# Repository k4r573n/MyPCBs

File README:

*******************************************
***   M y   P C B   L a y o u t s       ***
*******************************************

this will become an PCB Layout collection of Projects
I have done.

Since EAGLE provide XML-Files it is easy to use them
with version control systems what I'm doing here.

for suggestions or fixes contact me
Karsten Hinz <k.hinz@tu-bs.de>

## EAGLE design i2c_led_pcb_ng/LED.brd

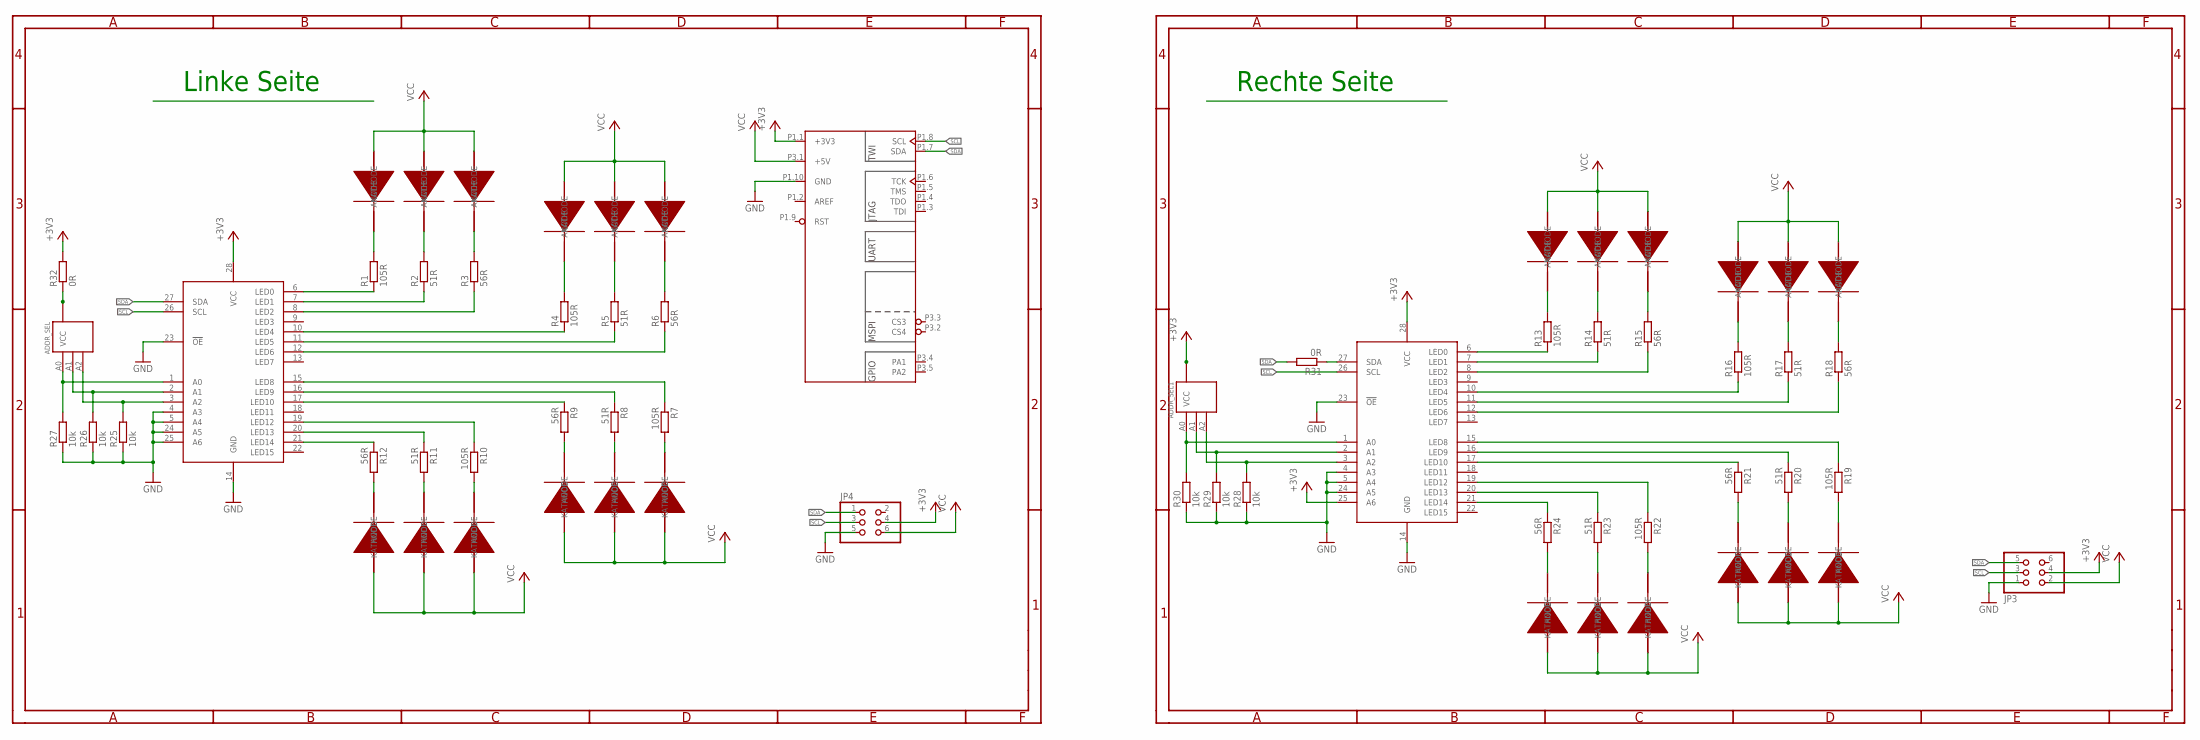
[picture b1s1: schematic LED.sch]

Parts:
ADDR_SEL, ADDR_SEL1: ADDR_SEL
JP3, JP4: PINHD-2X3_2.54-90°; 2X03/90
R1, R4, R7, R10, R13, R16, R19, R22: 105R; R0603
R2, R5, R8, R11, R14, R17, R20, R23: 51R; R0603
R3, R6, R9, R12, R15, R18, R21, R24: 56R; R0603
R25, R27: 10k; R0402
R26, R28, R29, R30: 10k; R0603
R31, R32: 0R; R0603
U$1, U$2, U$3, U$4, U$11, U$12, U$13, U$14: RGB-LED; PLCC_SMD_LED_RGB
U$6: INGA_OHNE_JP2; INGA_JP1_JP3
U$9, U$15: PCA9635; TSSOP28

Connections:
+3V3: JP3.4, JP4.4, R32.2, U$6.P1.1 (+3V3), U$9.28 (VCC), U$15.28 (VCC)
BLA: ADDR_SEL.VCC, ADDR_SEL.VCC@1 (VCC), ADDR_SEL.VCC@2 (VCC), R32.1
GND: JP3.1, JP4.5, R25.1, R26.1, R27.1, R28.1, R29.1, R30.1, U$6.P1.10 (GND), U$9.4 (A3), U$9.5 (A4), U$9.14 (GND), U$9.23 (!OE), U$9.24 (A5), U$9.25 (A6), U$15.4 (A3), U$15.5 (A4), U$15.14 (GND), U$15.23 (!OE), U$15.24 (A5)
unnamed: R1.1, U$9.6 (LED0)
unnamed: R2.1, U$9.7 (LED1)
unnamed: R3.1, U$9.8 (LED2)
unnamed: R4.1, U$9.10 (LED4)
unnamed: R5.1, U$9.11 (LED5)
unnamed: R6.1, U$9.12 (LED6)
unnamed: R7.1, U$9.15 (LED8)
unnamed: R8.1, U$9.16 (LED9)
unnamed: R9.1, U$9.17 (LED10)
unnamed: R10.1, U$9.19 (LED12)
unnamed: R11.1, U$9.20 (LED13)
unnamed: R12.1, U$9.21 (LED14)
unnamed: R12.2, U$4.P1 (KATHODE)
unnamed: R11.2, U$4.P2 (KATHODE)
unnamed: R10.2, U$4.P3 (KATHODE)
unnamed: R7.2, U$3.P3 (KATHODE)
unnamed: R8.2, U$3.P2 (KATHODE)
unnamed: R2.2, U$1.P2 (KATHODE)
unnamed: R1.2, U$1.P3 (KATHODE)
unnamed: R3.2, U$1.P1 (KATHODE)
unnamed: R4.2, U$2.P3 (KATHODE)
unnamed: R5.2, U$2.P2 (KATHODE)
unnamed: R6.2, U$2.P1 (KATHODE)
unnamed: R13.2, U$11.P3 (KATHODE)
unnamed: R13.1, U$15.6 (LED0)
unnamed: R14.1, U$15.7 (LED1)
unnamed: R15.1, U$15.8 (LED2)
unnamed: R16.1, U$15.10 (LED4)
unnamed: R17.1, U$15.11 (LED5)
unnamed: R18.1, U$15.12 (LED6)
unnamed: R19.1, U$15.15 (LED8)
unnamed: R20.1, U$15.16 (LED9)
unnamed: R21.1, U$15.17 (LED10)
unnamed: R22.1, U$15.19 (LED12)
unnamed: R23.1, U$15.20 (LED13)
unnamed: R24.1, U$15.21 (LED14)
unnamed: R14.2, U$11.P2 (KATHODE)
unnamed: R15.2, U$11.P1 (KATHODE)
unnamed: R16.2, U$12.P3 (KATHODE)
unnamed: R17.2, U$12.P2 (KATHODE)
unnamed: R18.2, U$12.P1 (KATHODE)
unnamed: R24.2, U$14.P1 (KATHODE)
unnamed: R23.2, U$14.P2 (KATHODE)
unnamed: R22.2, U$14.P3 (KATHODE)
unnamed: R21.2, U$13.P1 (KATHODE)
unnamed: R20.2, U$13.P2 (KATHODE)
unnamed: R19.2, U$13.P3 (KATHODE)
unnamed: R9.2, U$3.P1 (KATHODE)
unnamed: ADDR_SEL.A2, R25.2, U$9.3 (A2)
unnamed: ADDR_SEL.A1, R26.2, U$9.2 (A1)
unnamed: ADDR_SEL.A0, R27.2, U$9.1 (A0)
unnamed: ADDR_SEL1.A2, R28.2, U$15.3 (A2)
unnamed: ADDR_SEL1.A1, R29.2, U$15.2 (A1)
unnamed: ADDR_SEL1.A0, R30.2, U$15.1 (A0)
SCL: JP3.3, JP4.3, U$6.P1.8 (SCL), U$9.26 (SCL), U$15.26 (SCL)
SDA: JP3.5, JP4.1, R31.2, U$6.P1.7 (SDA), U$9.27 (SDA)
SDA@1: R31.1, U$15.27 (SDA)
VCC: ADDR_SEL1.VCC, ADDR_SEL1.VCC@1 (VCC), ADDR_SEL1.VCC@2 (VCC), JP3.2, JP4.6, U$1.P4 (ANODE), U$1.P5 (ANODE), U$1.P6 (ANODE), U$2.P4 (ANODE), U$2.P5 (ANODE), U$2.P6 (ANODE), U$3.P4 (ANODE), U$3.P5 (ANODE), U$3.P6 (ANODE), U$4.P4 (ANODE), U$4.P5 (ANODE), U$4.P6 (ANODE), U$6.P3.1 (+5V), U$11.P4 (ANODE), U$11.P5 (ANODE), U$11.P6 (ANODE), U$12.P4 (ANODE), U$12.P5 (ANODE), U$12.P6 (ANODE), U$13.P4 (ANODE), U$13.P5 (ANODE), U$13.P6 (ANODE), U$14.P4 (ANODE), U$14.P5 (ANODE), U$14.P6 (ANODE), U$15.25 (A6)

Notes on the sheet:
Linke Seite
Rechte Seite

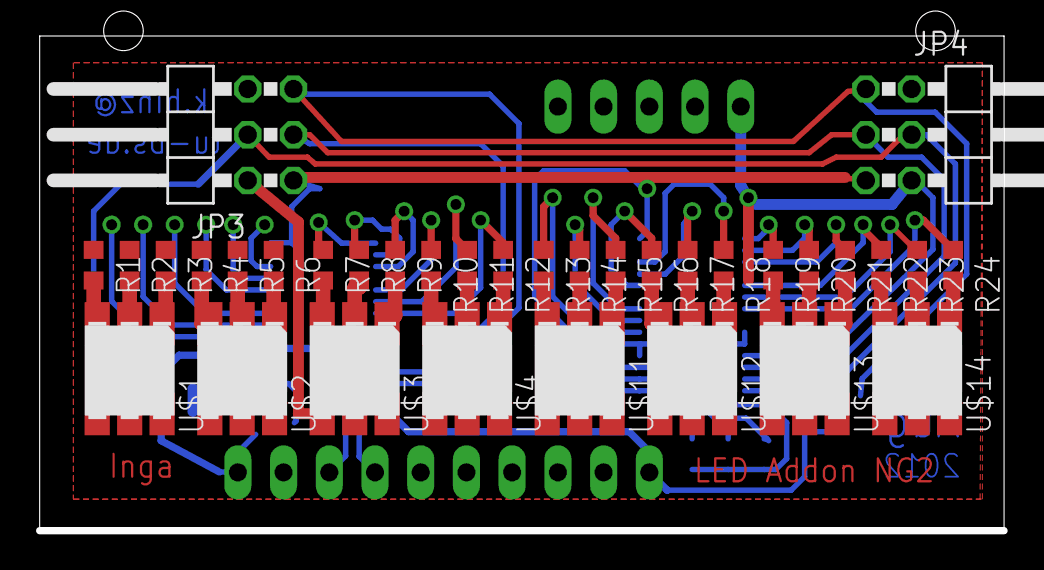
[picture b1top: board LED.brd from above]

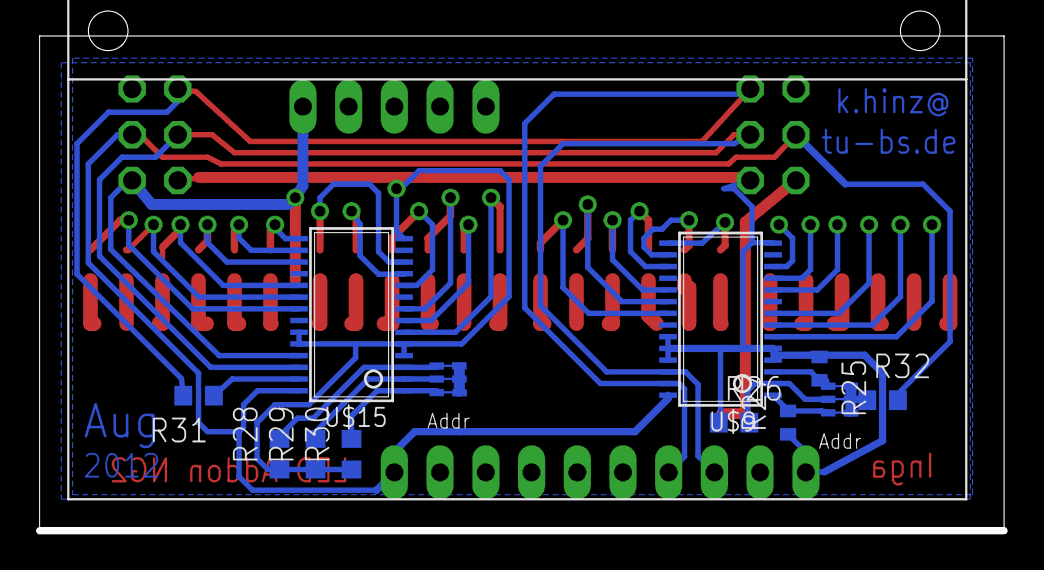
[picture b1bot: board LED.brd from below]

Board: 2 copper layers, 53.6 x 27.3 mm, 47 parts (13 on the bottom side), 61 nets.

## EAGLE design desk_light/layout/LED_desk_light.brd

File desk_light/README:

***************************
**   Bright Desk Light   **
***************************
by Volker and Karsten <k.hinz@tu-bs.de>

this should become an Desk Light with some nice Features:
- really bright (over 700lm)
- powersaving
- input pin for external brightness configuration
- easy to build
- cheap

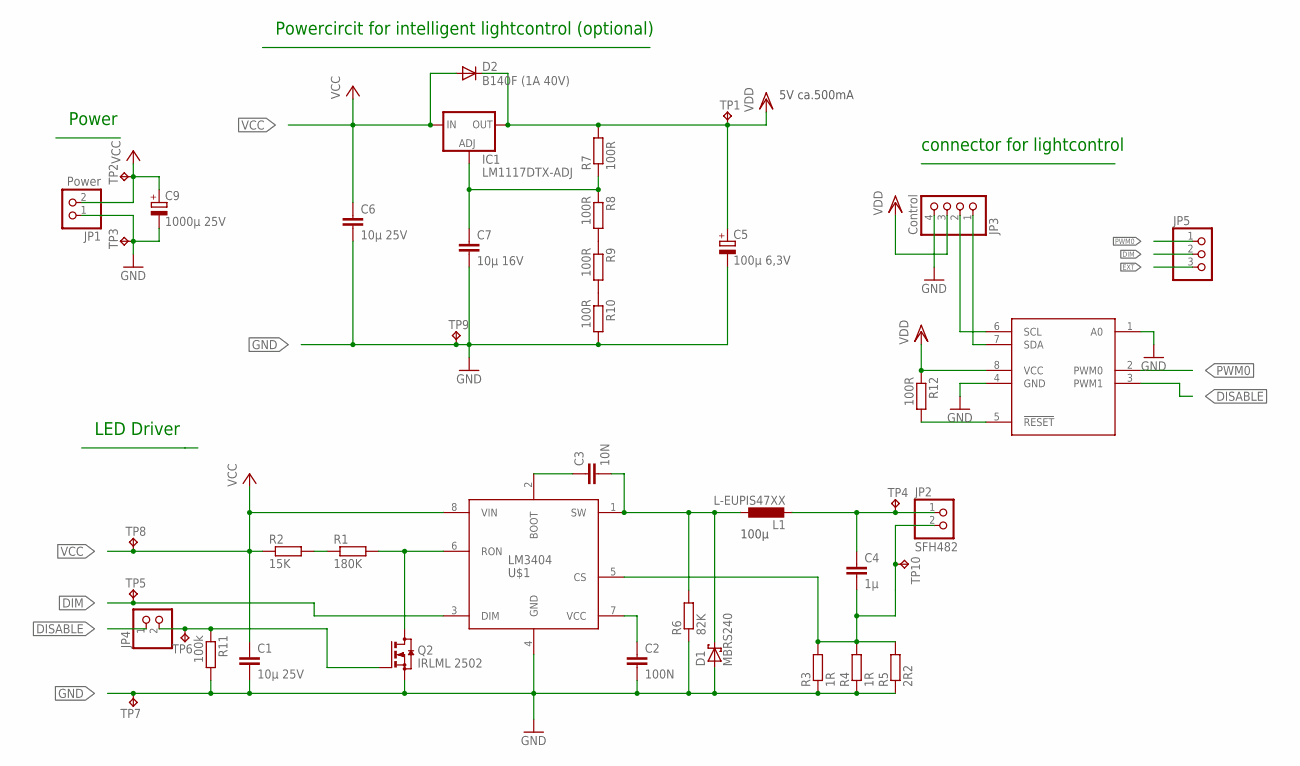
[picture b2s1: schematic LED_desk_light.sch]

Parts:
C1, C6: 10µ 25V; C1206
C2: 100N; C0805
C3: 10N; C0805
C4: 1µ; C0805
C5: 100µ 6,3V; SMC_D
C7: 10µ 16V; C1206
C9: 1000µ 25V; 153CLV-1014
D1: MBRS240; SMB
D2: B140F (1A 40V); DO214AC
IC1: LM1117DTX-ADJ; TO252
JP1: Power; 1X02SMD/90
JP2: SFH482; 1X02SMD/90
JP3: Control; 1X04SMD/90
JP4: PINHD-1X2_2.54; 1X02
JP5: PINHD-1X3_2.54; 1X03
L1: L-EUPIS47XX; PIS47XX
Q2: IRLML 2502; SOT23
R1: 180K; R0805
R2: 15K; R0805
R3, R4: 1R; R0805
R5: 2R2; R0805
R6: 82K; R0805
R7, R8, R9, R10, R12: 100R; R0805
R11: 100k; R0805
TP1, TP2, TP3, TP4, TP5, TP6, TP7, TP8, TP9, TP10: TP-040
U$1: LM3404; SO-8
U$2: PCA9530; SO08

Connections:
BLAAA: C5.+, D2.C, IC1.TAB (OUT), JP3.3, R7.2, R12.1, TP1.1, U$2.8 (VCC)
DABLE: JP4.2, Q2.1 (G), R11.1, TP6.1
DIM: JP5.2, TP5.1, U$1.3 (DIM)
DISABLE: JP4.1, U$2.3 (PWM1)
EXT: JP5.3
GND: C1.2, C2.2, C5.-, C6.2, C7.2, C9.-, D1.A, JP1.1, JP3.4, Q2.2 (S), R3.1, R4.1, R5.1, R6.1, R10.2, R11.2, TP3.1, TP7.1, TP9.1, U$1.4 (GND), U$2.1 (A0), U$2.4 (GND)
unnamed: R1.1, R2.2
unnamed: Q2.3 (D), R1.2, U$1.6 (RON)
unnamed: C2.1, U$1.7 (VCC)
unnamed: C4.1, JP2.1, L1.1 (2), TP4.1
unnamed: C3.1, U$1.2 (BOOT)
unnamed: C3.2, D1.C, L1.2 (1), R6.2, U$1.1 (SW)
unnamed: C4.2, JP2.2, R3.2, R4.2, R5.2, TP10.1, U$1.5 (CS)
unnamed: R12.2, U$2.5 (!RESET)
unnamed: JP3.1, U$2.7 (SDA)
unnamed: R8.2, R9.1
unnamed: R9.2, R10.1
unnamed: C7.1, IC1.1 (ADJ), R7.1, R8.1
PWM0: JP5.1, U$2.2 (PWM0)
SCL: JP3.2, U$2.6 (SCL)
VCC: C1.1, C6.1, C9.+, D2.A, IC1.2 (IN), JP1.2, R2.1, TP2.1, TP8.1, U$1.8 (VIN)

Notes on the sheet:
100µ
5V ca.500mA
connector for lightcontrol
Power
Powercircit for intelligent lightcontrol (optional)
LED Driver

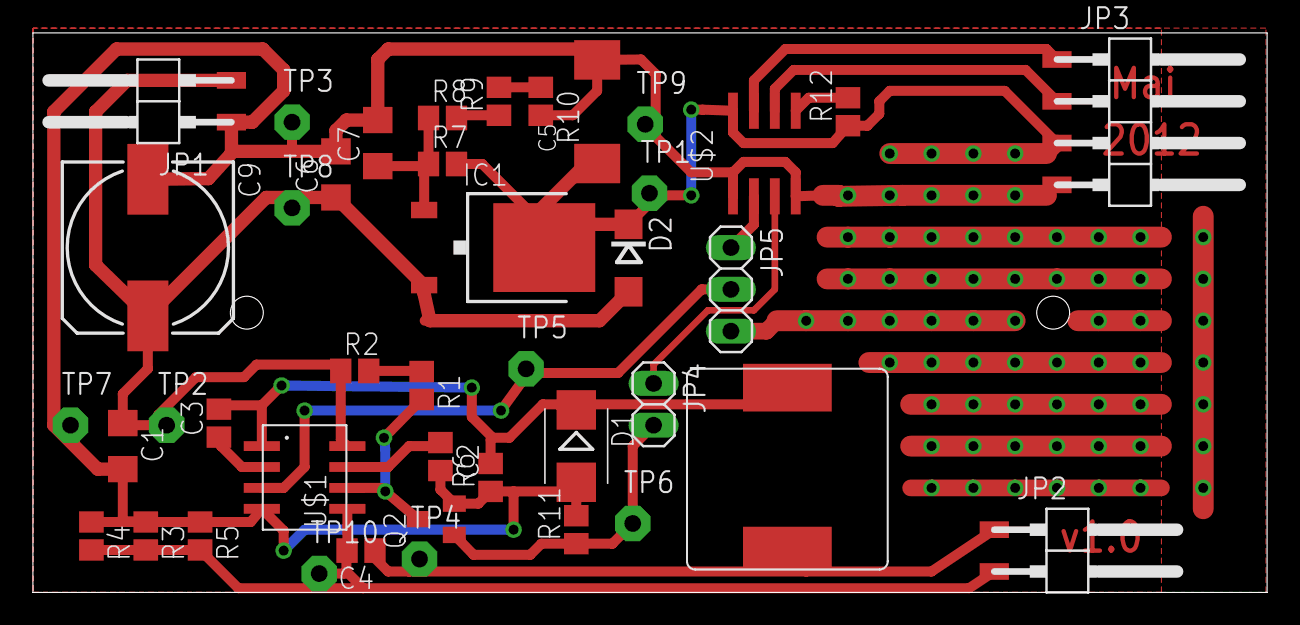
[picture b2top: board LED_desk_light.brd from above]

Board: 2 copper layers, 75.0 x 34.0 mm, 42 parts (0 on the bottom side), 20 nets.

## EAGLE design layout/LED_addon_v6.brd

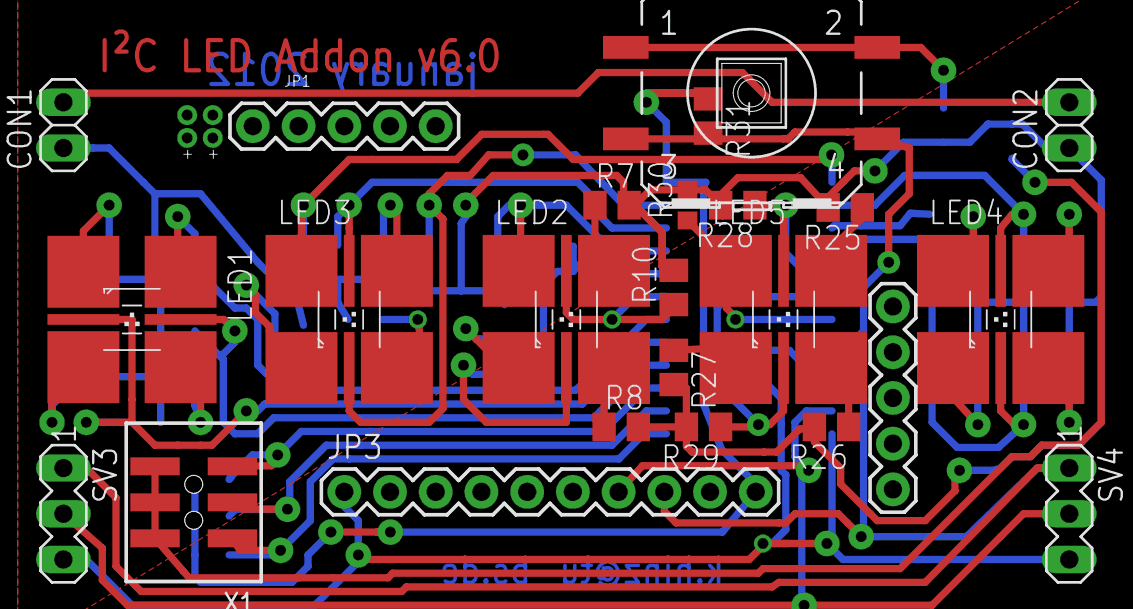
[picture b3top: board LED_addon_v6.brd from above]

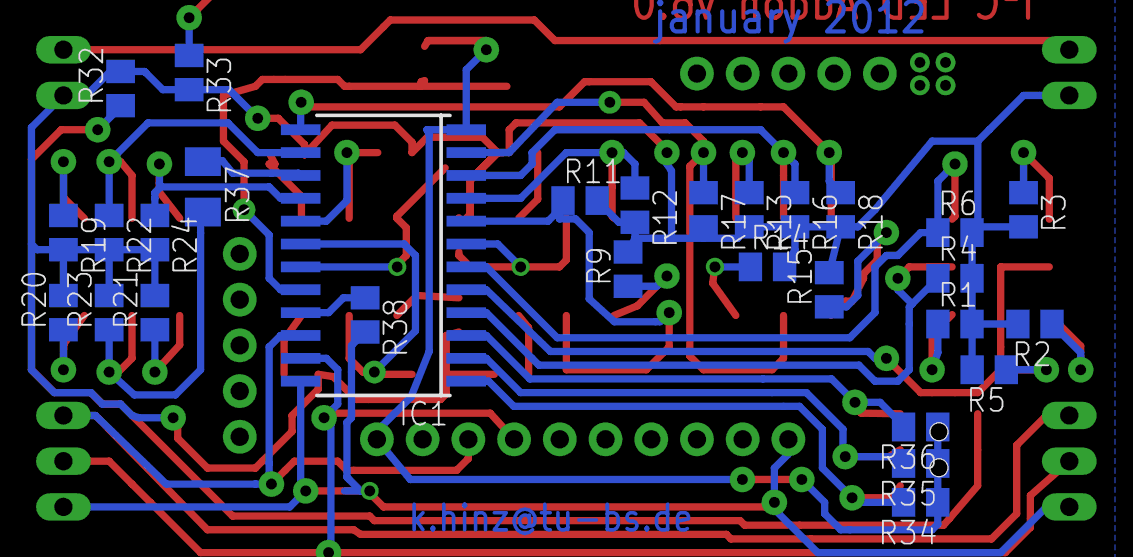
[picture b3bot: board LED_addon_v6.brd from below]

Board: 2 copper layers, 55 parts (29 on the bottom side), 43 nets.

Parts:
CON1, CON2: 1X02
IC1: PCA9532D; SO24
JP1: JP1; 1X05@1
JP2: JP2; 1X05@1
JP3: JP3; 1X10
JP4: Batt; BATT
JP5: Li-Ion; BATT
LED1, LED2, LED3, LED4, LED5: MULTILED_LRTB_G6TG; P-LCC-6_TOPLED
R1, R2, R7, R8, R13, R14, R19, R20, R25, R26: 40; M0805
R3, R9, R15, R21, R27: 95; M0805
R4, R5, R6, R10, R11, R12, R16, R17, R18, R22, R23, R24, R28, R29, R31, R32, R33, R34, R35, R36, R38: 100k; M0805
R30: 100k; R0603
R37: 0; M1206
SV3, SV4: MA03-1
U$2: TASTER
X1: 87832-06

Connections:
+3V3: IC1.24, JP3.1, R38.2, SV3.3, SV4.3
A0: IC1.1, R34.2, X1.1
A1: IC1.2, R35.2, X1.3
A2: IC1.3, R36.2, X1.5
GND: CON1.2, CON2.2, IC1.12, JP3.10, R31.1, R34.1, R35.1, R36.1
LED1B: IC1.4, LED1.C3, R4.1
LED1G: IC1.5, LED1.C2, R5.1
LED1R: IC1.6, LED1.C1, R6.1
LED2B: IC1.7, LED2.C3, R10.1
LED2G: IC1.8, LED2.C2, R11.1
LED2R: IC1.9, LED2.C1, R12.1
LED3B: IC1.10, LED3.C3, R16.1
LED3G: IC1.11, LED3.C2, R17.1
LED3R: IC1.13, LED3.C1, R18.1
LED4B: IC1.14, LED4.C3, R22.1
LED4G: IC1.15, R37.1
LED4G2: LED4.C2, R23.1, R37.2
LED4R: IC1.16, LED4.C1, R24.1
LED5B: IC1.17, LED5.C3, R28.1
LED5G: IC1.18, LED5.C2, R29.1
LED5R: IC1.19, LED5.C1, R30.1
unnamed: LED1.A3, R1.1
unnamed: LED1.A2, R2.1
unnamed: LED1.A1, R3.1
unnamed: IC1.21, R38.1
unnamed: R33.1, U$2.1, U$2.2
unnamed: R32.1, X1.2, X1.4, X1.6
unnamed: LED2.A3, R7.1
unnamed: LED2.A2, R8.1
unnamed: LED2.A1, R9.1
unnamed: LED3.A3, R13.1
unnamed: LED3.A2, R14.1
unnamed: LED3.A1, R15.1
unnamed: LED4.A3, R19.1
unnamed: LED4.A2, R20.1
unnamed: LED4.A1, R21.1
unnamed: LED5.A3, R25.1
unnamed: LED5.A2, R26.1
unnamed: LED5.A1, R27.1
SCL: IC1.22, JP3.8, SV3.1, SV4.1
SDA: IC1.23, JP3.7, SV3.2, SV4.2
SWITCH: IC1.20, R31.2, U$2.3, U$2.4
VCC: CON1.1, CON2.1, R1.2, R2.2, R3.2, R4.2, R5.2, R6.2, R7.2, R8.2, R9.2, R10.2, R11.2, R12.2, R13.2, R14.2, R15.2, R16.2, R17.2, R18.2, R19.2, R20.2, R21.2, R22.2, R23.2, R24.2, R25.2, R26.2, R27.2, R28.2, R29.2, R30.2, R32.2, R33.2

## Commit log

2012-01-20 layout fix: Via moved beside LEDs; added missed wire; added missed PullUp resistor at Reset; added doc
2012-01-20 restucture + readmes
2012-01-20 plans for LED Desk light
2012-01-22 first part of Layouting
2012-05-08 new generation of the i2C Addon Board
2012-06-12 changes to first prototype
2012-06-12 files as pdf
2012-06-12 rename of project files
2012-08-24 moved connector; bigger LED-pads for cooling; smaller address selector

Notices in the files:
parts and their libraries:
dframes: Copyright (C) 2004, Bob Starr (bobstarr@mindspring.com)
